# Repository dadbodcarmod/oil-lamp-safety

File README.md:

# oil-lamp-safety
A small circuit to cut power to the ECU if the oil dummy light is on too long.  No more blown engines.

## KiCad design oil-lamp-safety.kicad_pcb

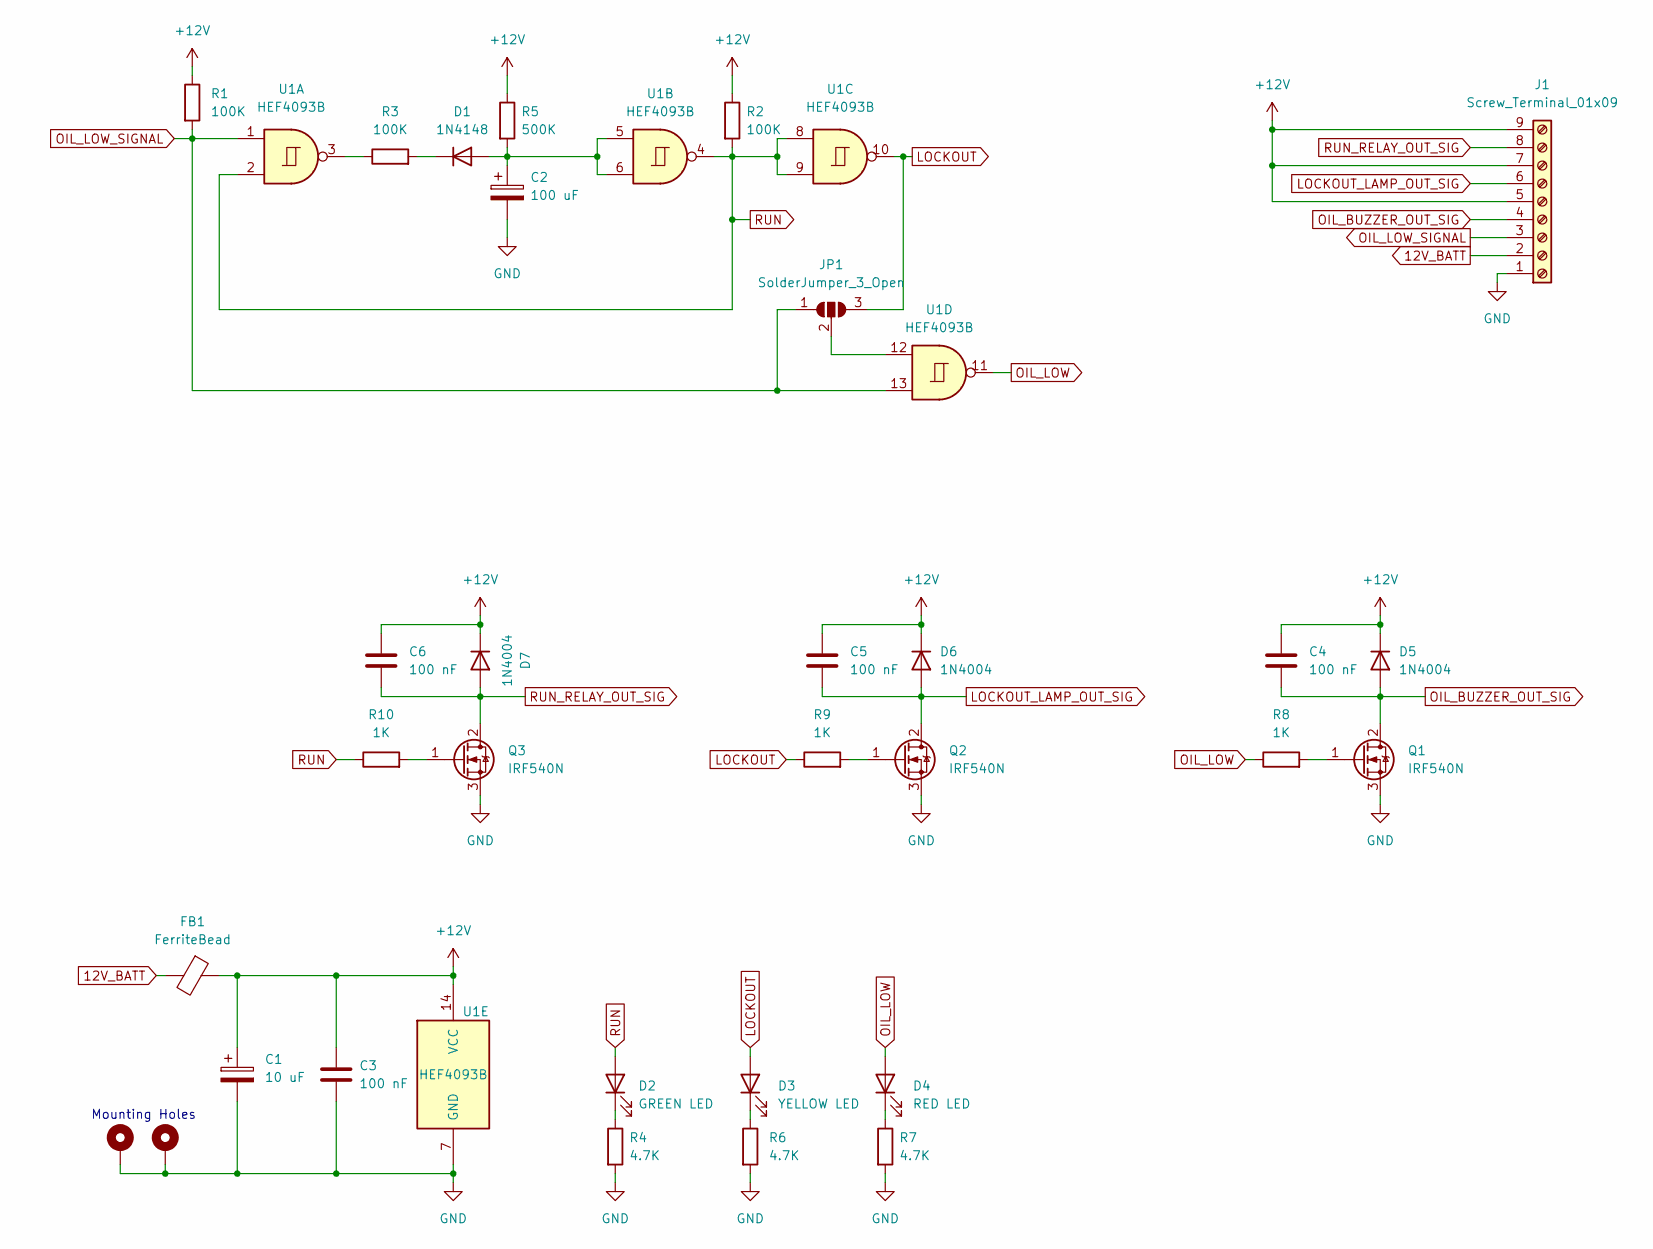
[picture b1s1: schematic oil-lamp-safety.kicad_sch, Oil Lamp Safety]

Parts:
C1: 10 uF; CP_Radial_D6.3mm_P2.50mm
C2: 100 uF; CP_Radial_D10.0mm_P5.00mm
C3, C4, C5, C6: 100 nF; C_Rect_L7.2mm_W3.0mm_P5.00mm_FKS2_FKP2_MKS2_MKP2
D1: 1N4148; D_DO-35_SOD27_P12.70mm_Horizontal
D2: GREEN LED; LED_D5.0mm
D3: YELLOW LED; LED_D5.0mm
D4: RED LED; LED_D5.0mm
D5, D6, D7: 1N4004; D_DO-41_SOD81_P12.70mm_Horizontal
FB1: FerriteBead; R_Box_L13.0mm_W4.0mm_P9.00mm
H1, H2: MountingHole_Pad; MountingHole_5.3mm_M5_Pad
J1: Screw_Terminal_01x09; TerminalBlock_4Ucon_1x09_P3.50mm_Horizontal
JP1: SolderJumper_3_Open; SolderJumper-3_P1.3mm_Open_RoundedPad1.0x1.5mm
Q1, Q2, Q3: IRF540N; TO-220-3_Vertical
R1, R2, R3: 100K; R_Axial_DIN0309_L9.0mm_D3.2mm_P12.70mm_Horizontal
R4, R6, R7: 4.7K; R_Axial_DIN0309_L9.0mm_D3.2mm_P12.70mm_Horizontal
R5: 500K; R_Axial_DIN0309_L9.0mm_D3.2mm_P12.70mm_Horizontal
R8, R9, R10: 1K; R_Axial_DIN0309_L9.0mm_D3.2mm_P12.70mm_Horizontal
U1: HEF4093B; DIP-14_W7.62mm_LongPads

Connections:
12V_BATT: FB1.2, J1.2
+12V: C1.1, C3.1, C4.1, C5.1, C6.1, D5.1 (K), D6.1 (K), D7.1 (K), FB1.1, J1.5, J1.7, J1.9, R1.1, R2.1, R5.1, U1.14 (VCC)
GND: C1.2, C2.2, C3.2, H1.1, H2.1, J1.1, Q1.3 (S), Q2.3 (S), Q3.3 (S), R4.2, R6.2, R7.2, U1.7 (GND)
LOCKOUT: D3.2 (A), JP1.3 (B), R9.1, U1.10
LOCKOUT_LAMP_OUT_SIG: C5.2, D6.2 (A), J1.6, Q2.2 (D)
unnamed: C2.1, D1.2 (A), R5.2, U1.5, U1.6
unnamed: D1.1 (K), R3.2
unnamed: D2.1 (K), R4.1
unnamed: D3.1 (K), R6.1
unnamed: D4.1 (K), R7.1
unnamed: JP1.2 (C), U1.12
unnamed: Q1.1 (G), R8.2
unnamed: Q2.1 (G), R9.2
unnamed: Q3.1 (G), R10.2
unnamed: R3.1, U1.3
OIL_BUZZER_OUT_SIG: C4.2, D5.2 (A), J1.4, Q1.2 (D)
OIL_LOW: D4.2 (A), R8.1, U1.11
OIL_LOW_SIGNAL: J1.3, JP1.1 (A), R1.2, U1.1, U1.13
RUN: D2.2 (A), R2.2, R10.1, U1.2, U1.4, U1.8, U1.9
RUN_RELAY_OUT_SIG: C6.2, D7.2 (A), J1.8, Q3.2 (D)

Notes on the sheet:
Mounting Holes

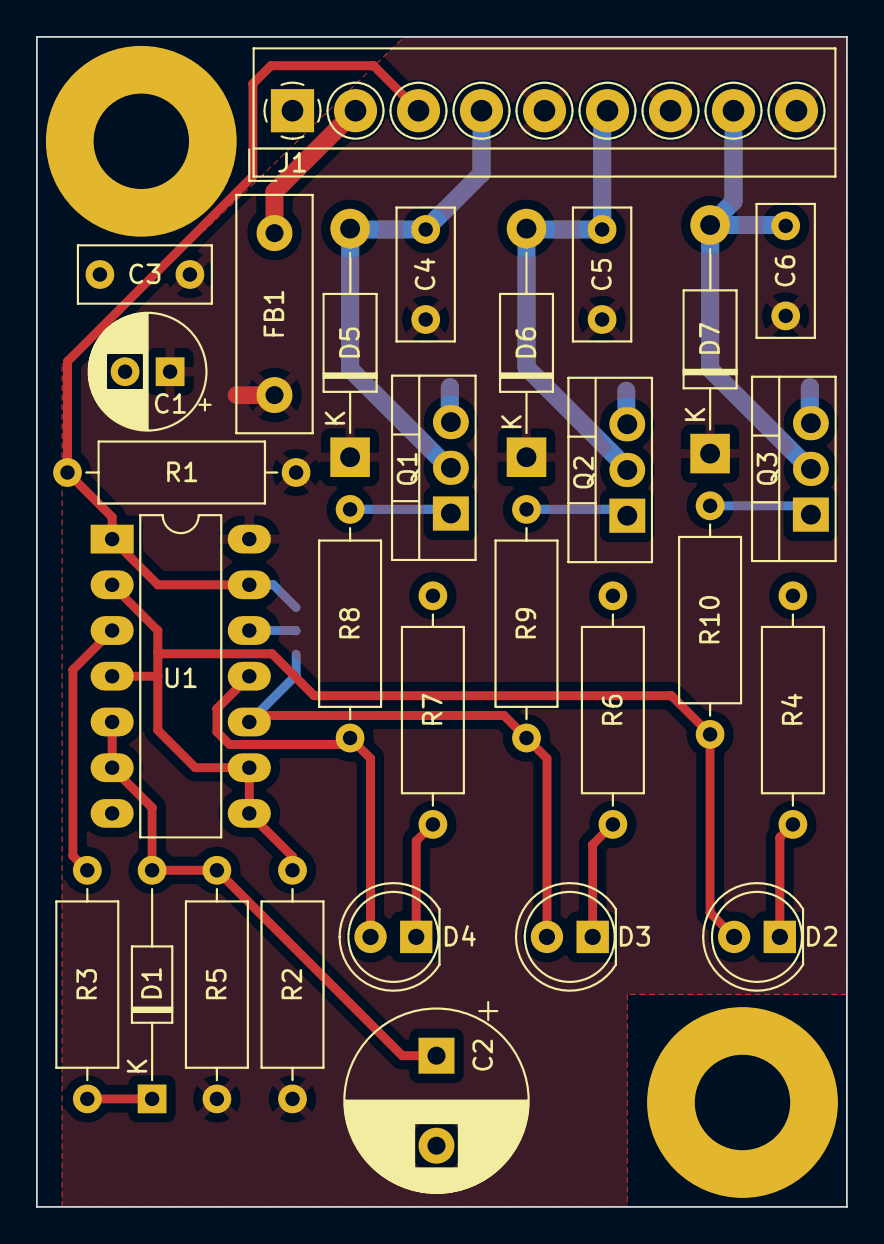
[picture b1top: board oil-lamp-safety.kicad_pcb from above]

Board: 2 copper layers, 45.0 x 65.0 mm, 32 parts (1 on the bottom side), 20 nets.

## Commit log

2024-08-09 Adding first version of the project.
2024-08-14 Updated the design to fix lockout on power up issue.
